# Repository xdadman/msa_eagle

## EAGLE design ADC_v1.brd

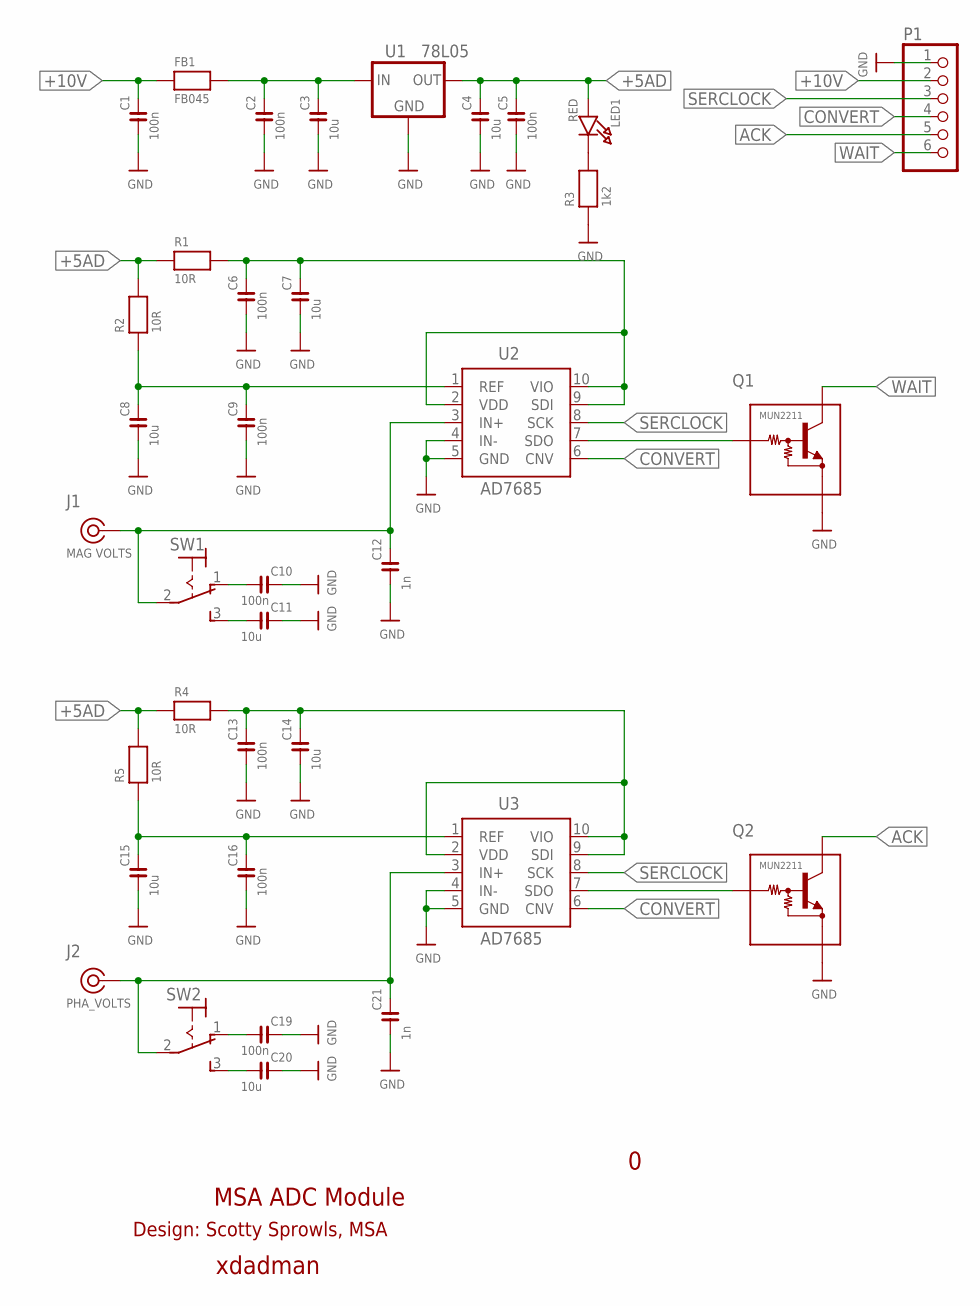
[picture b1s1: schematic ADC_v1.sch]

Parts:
C1, C2, C5, C6, C9, C10, C13, C16, C19: 100n; C0805
C3, C4, C7, C8, C11, C14, C15, C20: 10u; C1206
C12, C21: 1n; C0805
FB1: FB045; R0805
J1: MAG VOLTS; SLIM_COAX_PAD
J2: PHA_VOLTS; SLIM_COAX_PAD
LED1: RED; CHIPLED_0603
P1: PINHD-1X6; 1X06
Q1, Q2: MUN2211; SOT23
R1, R2, R4, R5: 10R; R0805
R3: 1k2; R0805
SW1, SW2: SWITCH1AS3; 1AS3T2B4M2RE
U1: 78L05; SOT89
U2, U3: AD7685; MSOP10

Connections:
+5AD: C4.2, C5.2, LED1.A, R1.1, R2.2, R4.1, R5.2, U1.1 (OUT)
+10V: C1.2, FB1.1, P1.2
ACK: P1.5, Q2.C
CONVERT: P1.4, U2.6 (CNV), U3.6 (CNV)
GND: C1.1, C2.1, C3.1, C4.1, C5.1, C6.1, C7.1, C8.1, C9.1, C10.2, C11.2, C12.1, C13.1, C14.1, C15.1, C16.1, C19.2, C20.2, C21.1, J1.GND, J2.GND, P1.1, Q1.E, Q2.E, R3.1, U1.2 (GND), U1.4 (GND), U2.4 (IN-), U2.5 (GND), U3.4 (IN-), U3.5 (GND)
unnamed: C2.2, C3.2, FB1.2, U1.3 (IN)
unnamed: C8.2, C9.2, R2.1, U2.1 (REF)
unnamed: C6.2, C7.2, R1.2, U2.2 (VDD), U2.9 (SDI), U2.10 (VIO)
unnamed: LED1.C, R3.2
unnamed: Q1.B, U2.7 (SDO)
unnamed: C15.2, C16.2, R5.1, U3.1 (REF)
unnamed: C12.2, J1.SIG (1), SW1.2, U2.3 (IN+)
unnamed: C11.1, SW1.3 (S)
unnamed: C10.1, SW1.1 (O)
unnamed: C13.2, C14.2, R4.2, U3.2 (VDD), U3.9 (SDI), U3.10 (VIO)
unnamed: Q2.B, U3.7 (SDO)
unnamed: C21.2, J2.SIG (1), SW2.2, U3.3 (IN+)
unnamed: C20.1, SW2.3 (S)
unnamed: C19.1, SW2.1 (O)
SERCLOCK: P1.3, U2.8 (SCK), U3.8 (SCK)
WAIT: P1.6, Q1.C

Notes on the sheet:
xdadman
MSA ADC Module
Design: Scotty Sprowls, MSA

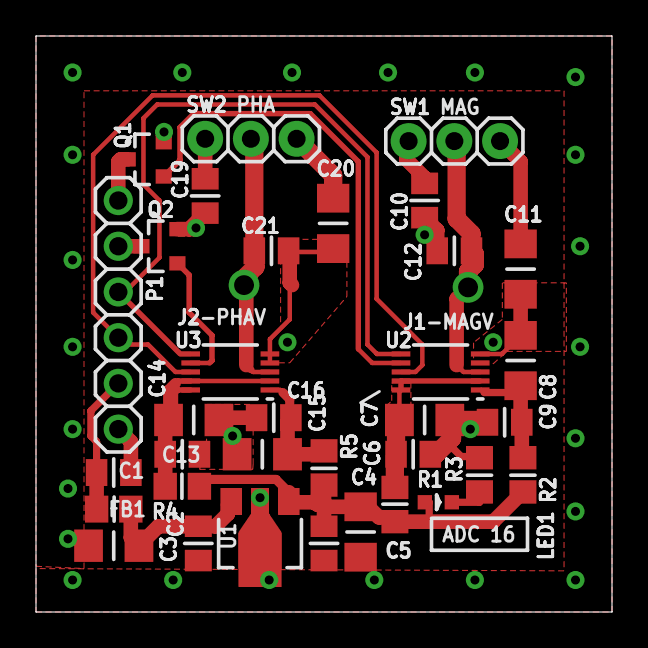
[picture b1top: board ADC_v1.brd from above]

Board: 2 copper layers, 32.0 x 32.0 mm, 36 parts (0 on the bottom side), 21 nets.

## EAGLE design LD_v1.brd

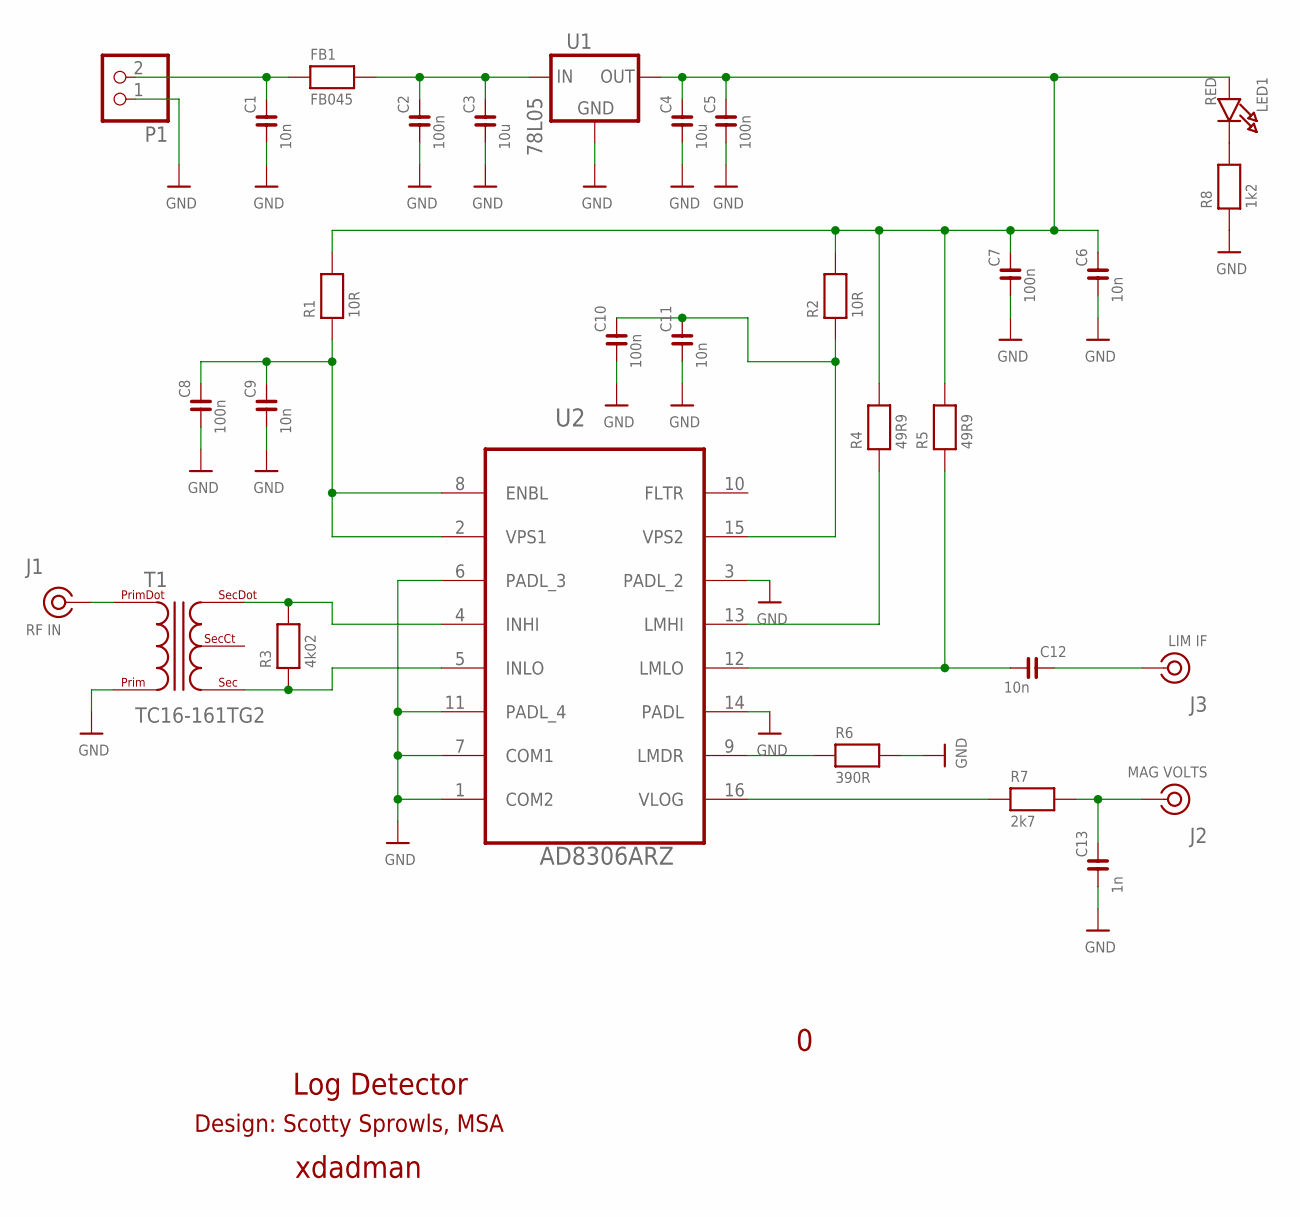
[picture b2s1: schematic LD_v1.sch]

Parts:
C1, C6, C9, C11, C12: 10n; C0805
C2, C5, C7, C8, C10: 100n; C0805
C3, C4: 10u; C1206
C13: 1n; C0805
FB1: FB045; R0805
J1: RF IN; SLIM_COAX_PAD
J2: MAG VOLTS; SLIM_COAX_PAD
J3: LIM IF; SLIM_COAX_PAD
LED1: RED; CHIPLED_0603
P1: PINHD-1X2; 1X02
R1, R2: 10R; R0805
R3: 4k02; R0805
R4, R5: 49R9; R0805
R6: 390R; R0805
R7: 2k7; R0805
R8: 1k2; R0805
T1: TC16-161TG2
U1: 78L05; SOT89
U2: AD8306ARZ; SOIC16

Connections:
+5V: C4.2, C5.2, C6.2, C7.2, LED1.A, R1.2, R2.2, R4.2, R5.2, U1.1 (OUT)
+10V: C1.2, FB1.1, P1.2
GND: C1.1, C2.1, C3.1, C4.1, C5.1, C6.1, C7.1, C8.1, C9.1, C10.1, C11.1, C13.1, J1.GND, J2.GND, J3.GND, P1.1, R6.2, R8.1, T1.4, U1.2 (GND), U1.4 (GND), U2.1 (COM2), U2.3 (PADL_2), U2.6 (PADL_3), U2.7 (COM1), U2.11 (PADL_4), U2.14 (PADL)
unnamed: C2.2, C3.2, FB1.2, U1.3 (IN)
unnamed: C8.2, C9.2, R1.1, U2.2 (VPS1), U2.8 (ENBL)
unnamed: R4.1, U2.13 (LMHI)
unnamed: C13.2, J2.SIG (1), R7.2
unnamed: C12.1, R5.1, U2.12 (LMLO)
unnamed: C12.2, J3.SIG (1)
unnamed: R3.2, T1.1, U2.4 (INHI)
unnamed: R3.1, T1.3, U2.5 (INLO)
unnamed: J1.SIG (1), T1.6
unnamed: R6.1, U2.9 (LMDR)
unnamed: R7.1, U2.16 (VLOG)
unnamed: LED1.C, R8.2
unnamed: C10.2, C11.2, R2.1, U2.15 (VPS2)

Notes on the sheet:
xdadman
Log Detector
Design: Scotty Sprowls, MSA

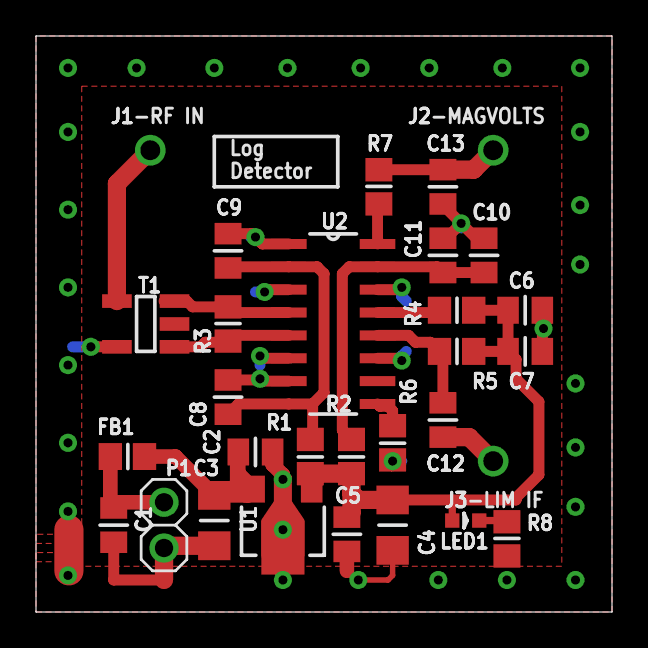
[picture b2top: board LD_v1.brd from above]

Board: 2 copper layers, 32.0 x 32.0 mm, 30 parts (0 on the bottom side), 16 nets.

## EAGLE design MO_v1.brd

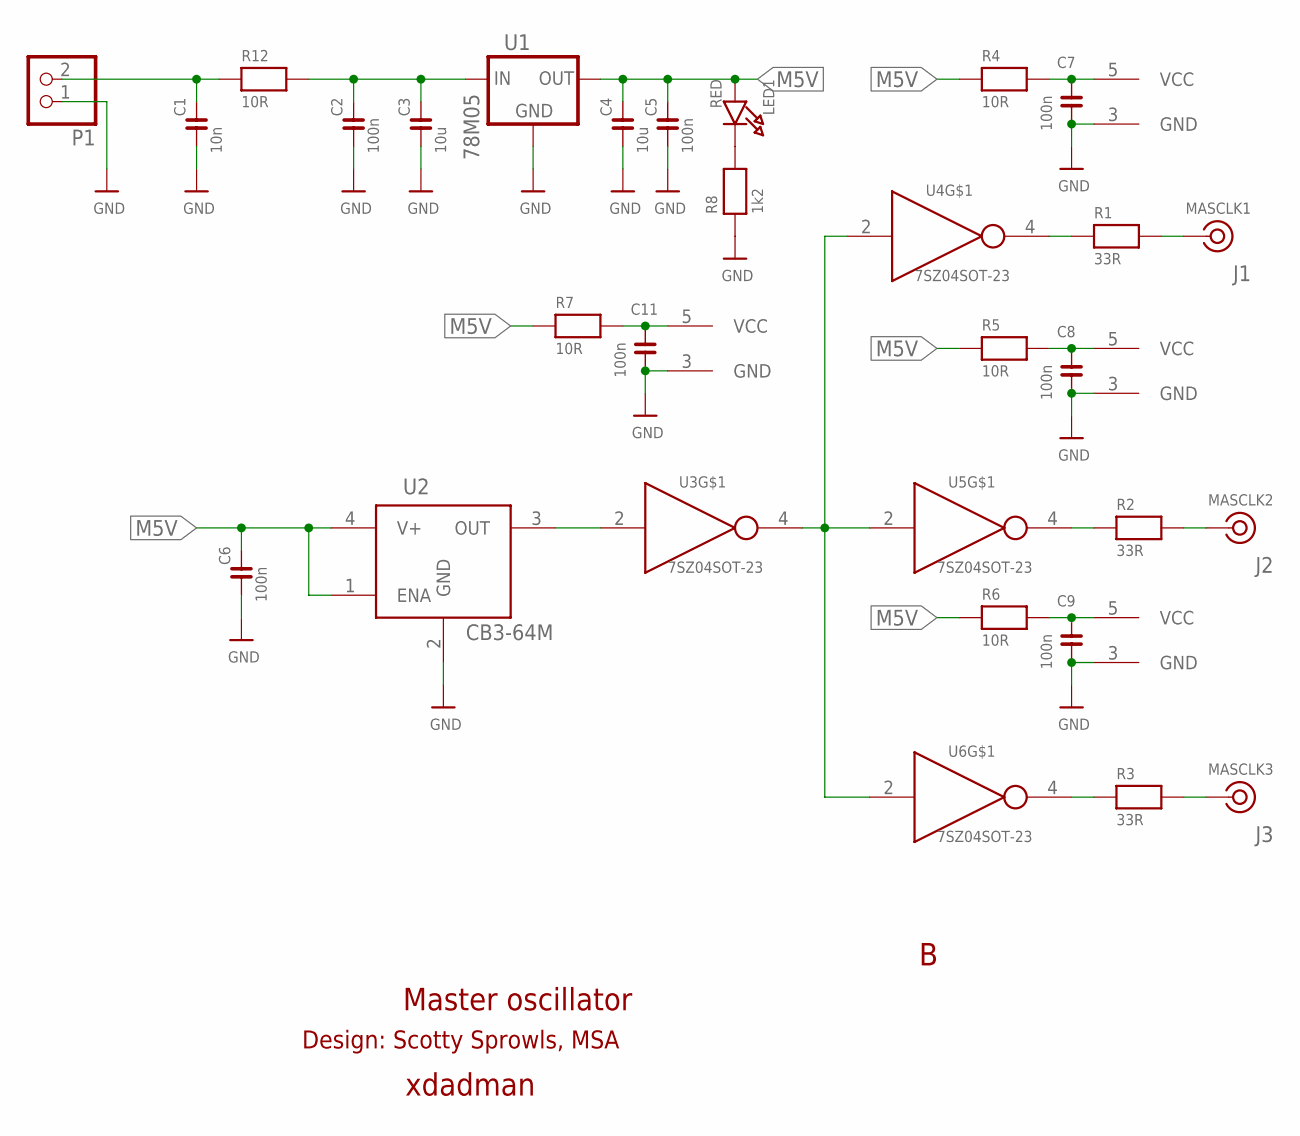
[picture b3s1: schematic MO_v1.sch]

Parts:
C1: 10n; C0805
C2, C5, C6, C7, C8, C9, C11: 100n; C0805
C3, C4: 10u; C1206
J1: MASCLK1; SLIM_COAX_PAD
J2: MASCLK2; SLIM_COAX_PAD
J3: MASCLK3; SLIM_COAX_PAD
LED1: RED; CHIPLED_0603
P1: PINHD-1X2; 1X02
R1, R2, R3: 33R; R0805
R4, R5, R6, R7, R12: 10R; R0805
R8: 1k2; R0805
U1: 78M05; TO252
U2: CB3-64M
U3, U4, U5, U6: 7SZ04SOT-23; SOT23-5L

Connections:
+10V: C1.2, P1.2, R12.1
GND: C1.1, C2.1, C3.1, C4.1, C5.1, C6.1, C7.1, C8.1, C9.1, C11.1, J1.GND, J2.GND, J3.GND, P1.1, R8.1, U1.3 (GND), U2.2 (GND), U3.3 (GND), U4.3 (GND), U5.3 (GND), U6.3 (GND)
M5V: C4.2, C5.2, C6.2, LED1.A, R4.1, R5.1, R6.1, R7.1, U1.2 (OUT), U2.1 (ENA), U2.4 (V+)
unnamed: C2.2, C3.2, R12.2, U1.1 (IN)
unnamed: U2.3 (OUT), U3.2 (IN)
unnamed: C7.2, R4.2, U4.5 (VCC)
unnamed: C11.2, R7.2, U3.5 (VCC)
unnamed: C8.2, R5.2, U5.5 (VCC)
unnamed: U3.4 (OUT), U4.2 (IN), U5.2 (IN), U6.2 (IN)
unnamed: C9.2, R6.2, U6.5 (VCC)
unnamed: R1.1, U4.4 (OUT)
unnamed: R2.1, U5.4 (OUT)
unnamed: R3.1, U6.4 (OUT)
unnamed: J3.SIG (1), R3.2
unnamed: J2.SIG (1), R2.2
unnamed: J1.SIG (1), R1.2
unnamed: LED1.C, R8.2

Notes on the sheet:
xdadman
Master oscillator
Design: Scotty Sprowls, MSA

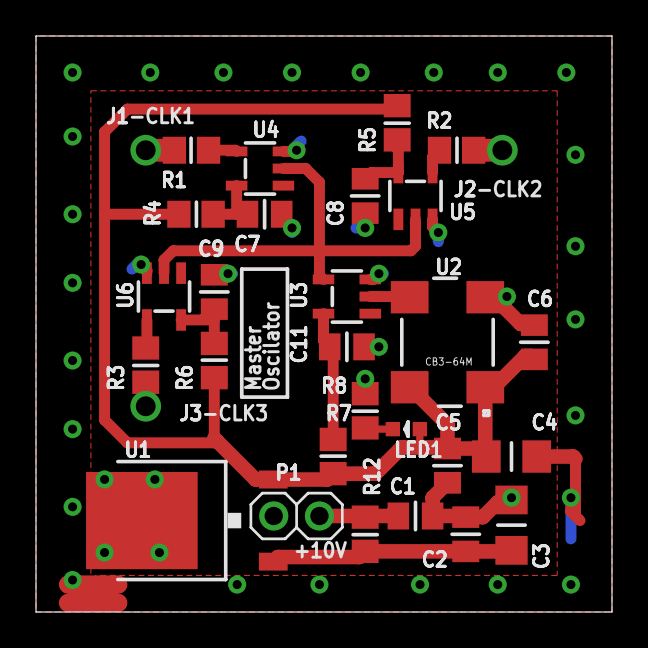
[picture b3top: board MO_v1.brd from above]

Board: 2 copper layers, 32.0 x 32.0 mm, 30 parts (0 on the bottom side), 17 nets.

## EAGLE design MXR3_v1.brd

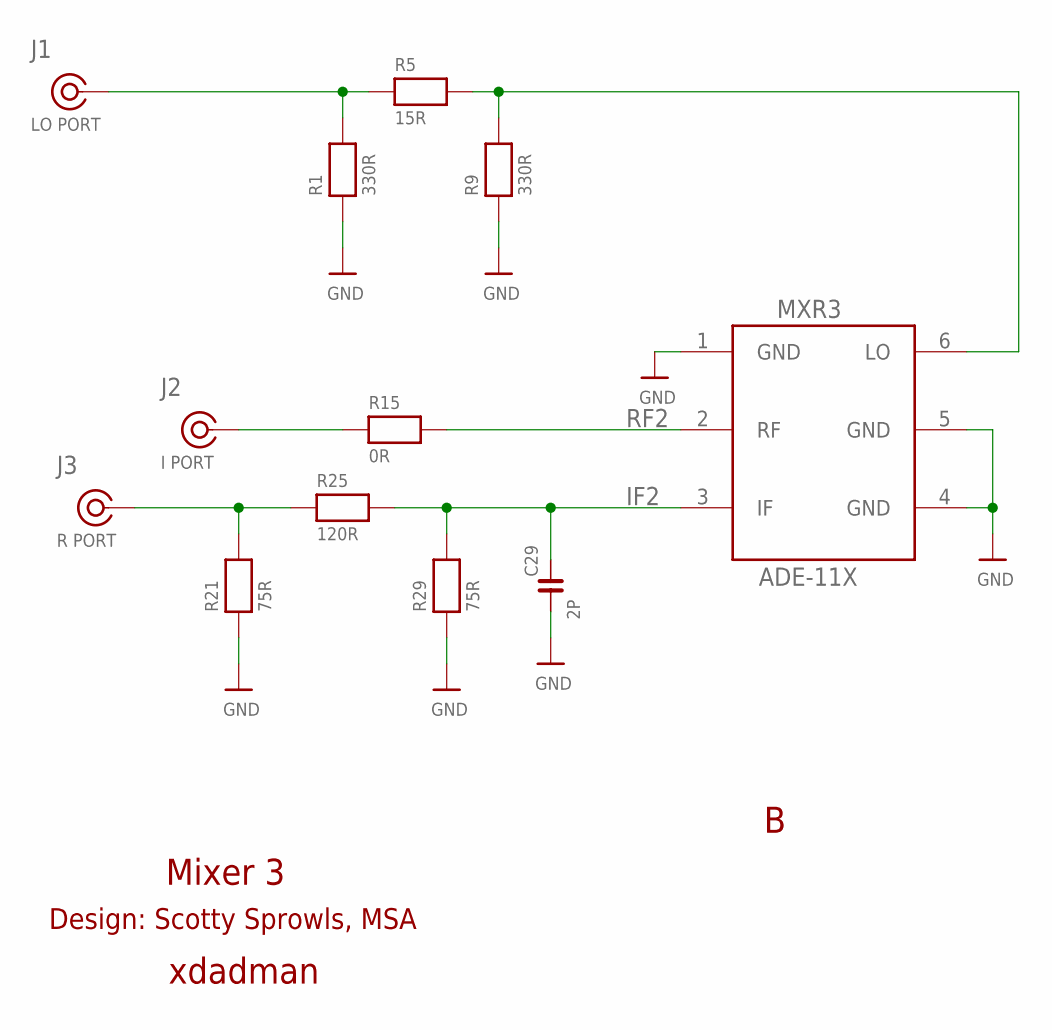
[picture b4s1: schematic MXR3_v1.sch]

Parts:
C29: 2P; C0603
J1: LO PORT; SLIM_COAX_PAD
J2: I PORT; SLIM_COAX_PAD
J3: R PORT; SLIM_COAX_PAD
MXR3: ADE-11X
R1, R9: 330R; R0805
R5: 15R; 0805
R15: 0R; R0805
R21, R29: 75R; R0805
R25: 120R; R0805

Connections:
GND: C29.1, J1.GND, J2.GND, J3.GND, MXR3.1 (GND), MXR3.4 (GND), MXR3.5 (GND), R1.1, R9.1, R21.1, R29.1
IF: J3.SIG (1), R21.2, R25.1
IF2: C29.2, MXR3.3 (IF), R25.2, R29.2
LO: J1.SIG (1), R1.2, R5.1
LO3: MXR3.6 (LO), R5.2, R9.2
RF: J2.SIG (1), R15.1
RF2: MXR3.2 (RF), R15.2

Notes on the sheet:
xdadman
Mixer 3
Design: Scotty Sprowls, MSA

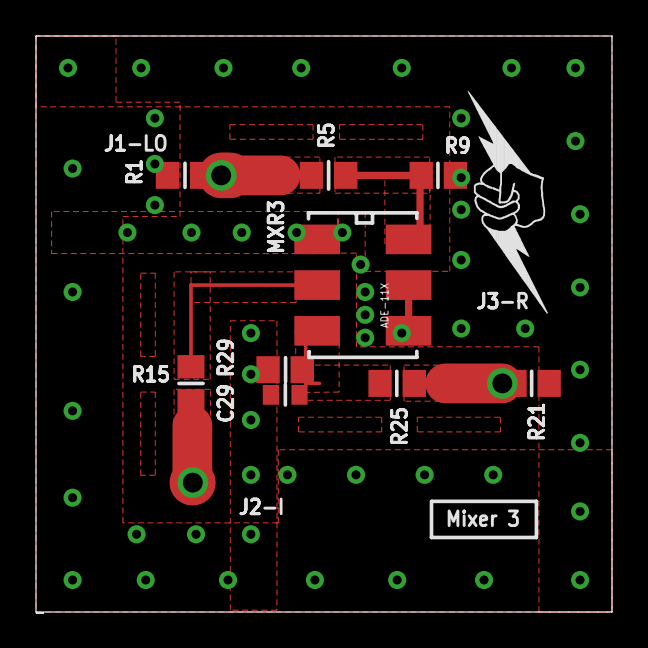
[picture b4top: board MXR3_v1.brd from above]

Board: 2 copper layers, 32.0 x 32.0 mm, 12 parts (0 on the bottom side), 7 nets.

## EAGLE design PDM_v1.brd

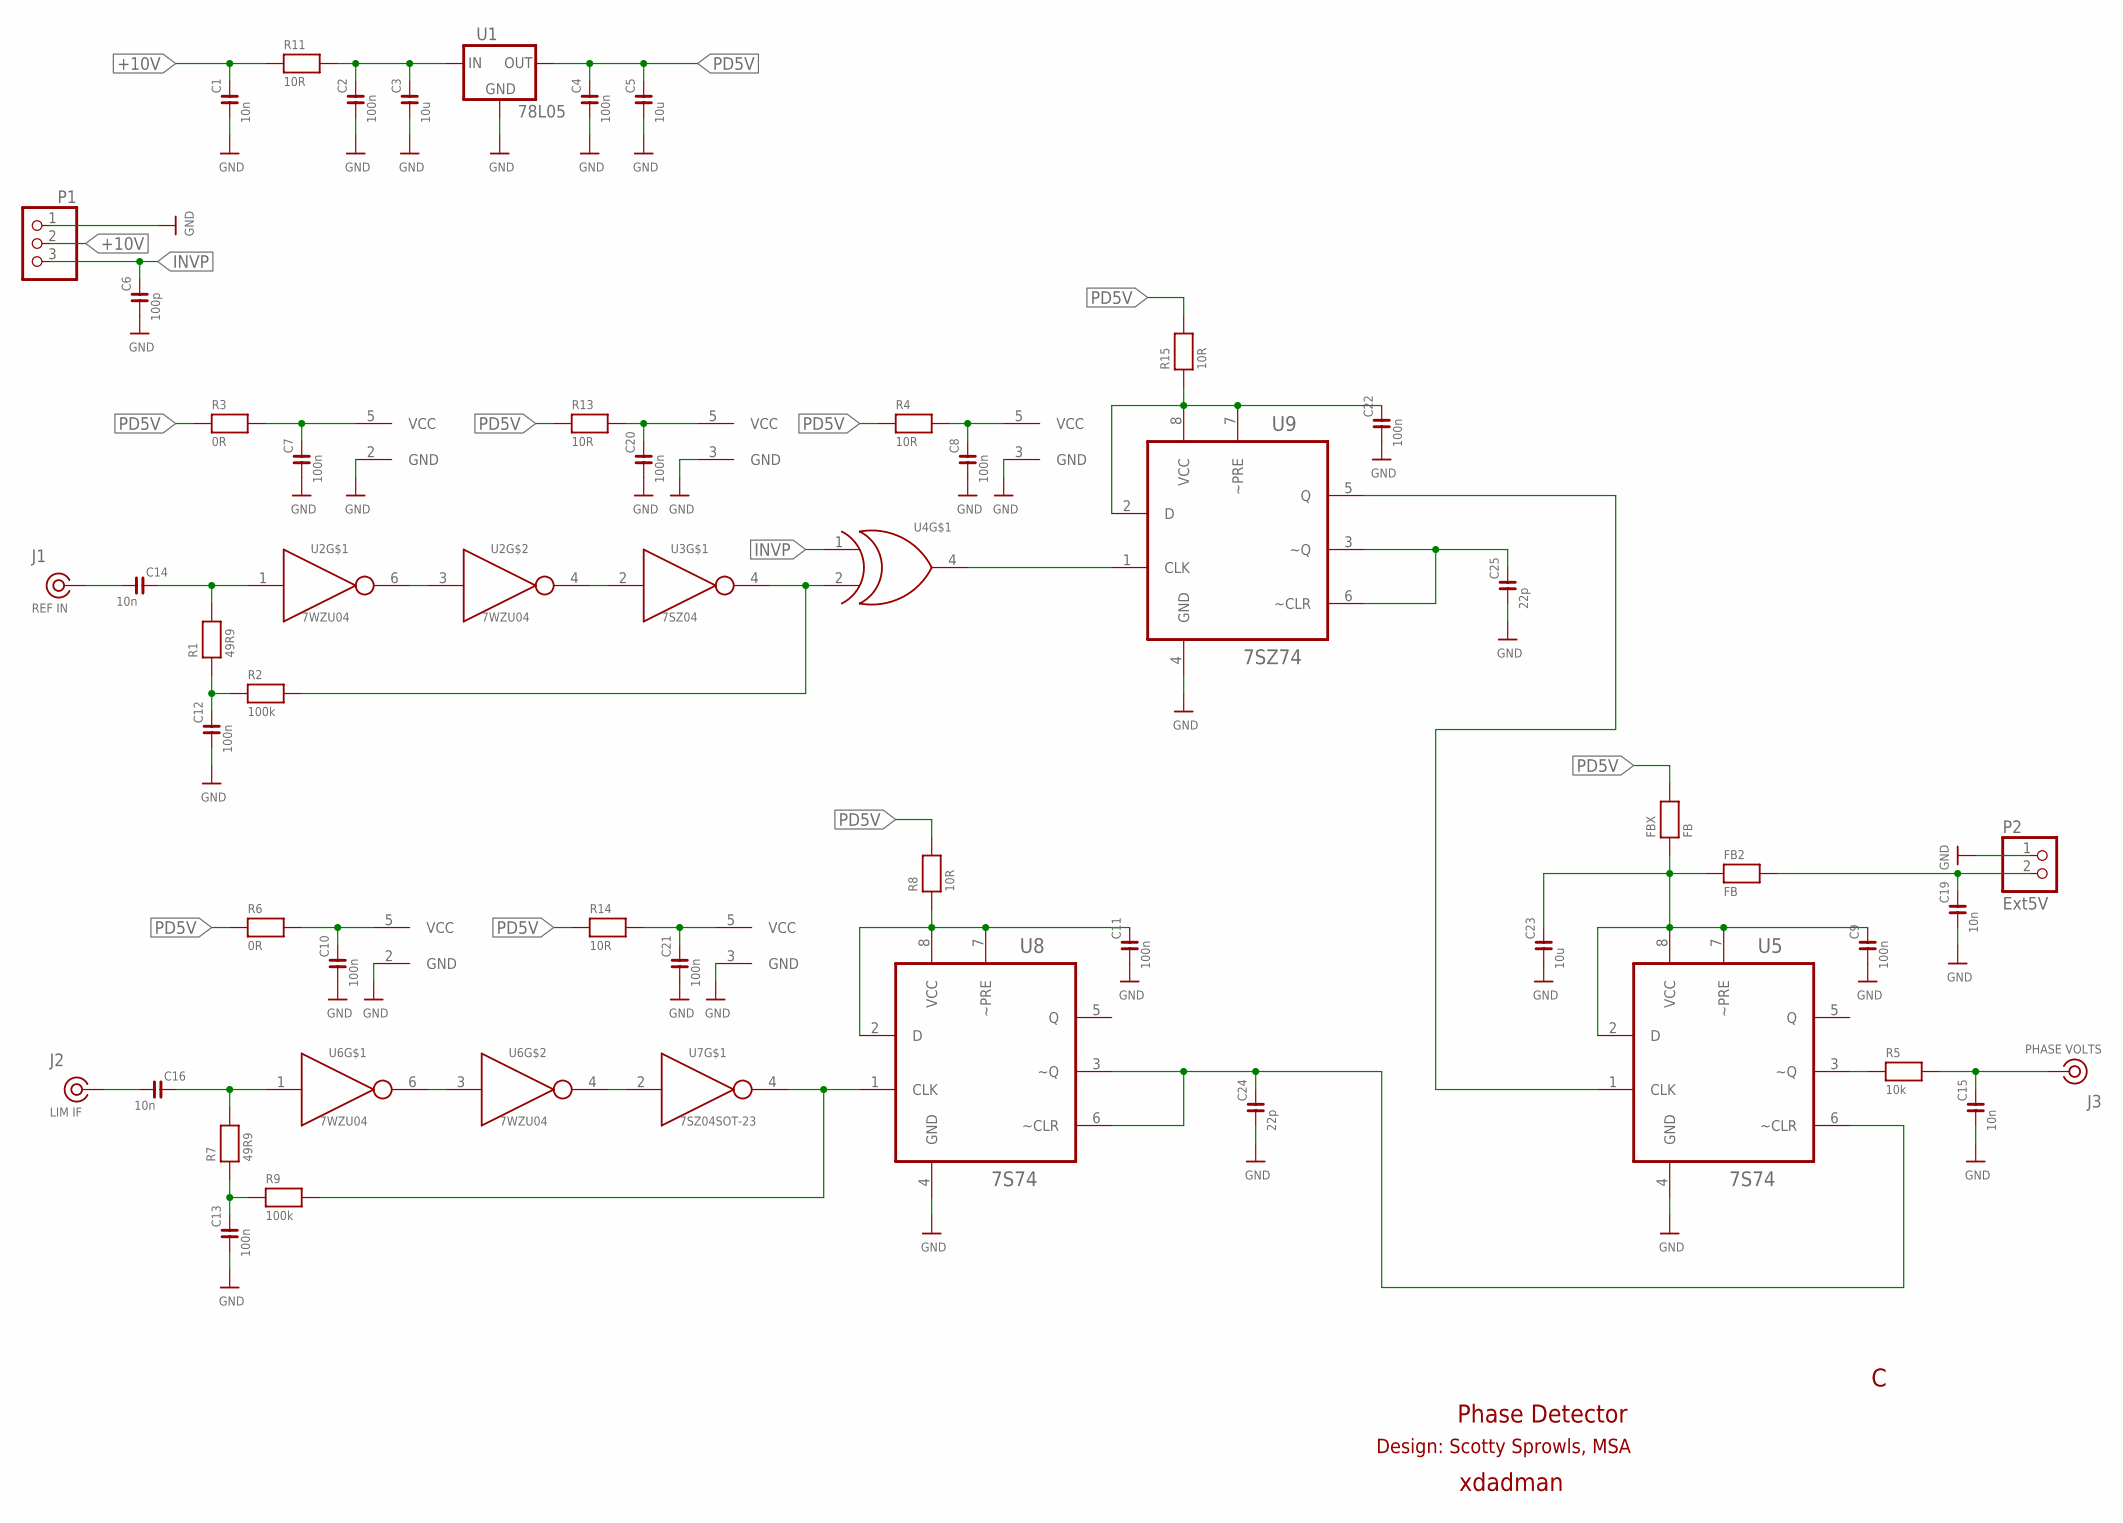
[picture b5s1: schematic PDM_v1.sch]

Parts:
C1, C14, C15, C16, C19: 10n; C0805
C2, C4, C7, C8, C9, C10, C11, C12, C13, C20, C21, C22: 100n; C0805
C3, C5, C23: 10u; C1206
C6: 100p; C0805
C24, C25: 22p; C0603
FB2: FB; R0805
FBX: FB; R0805
J1: REF IN; SLIM_COAX_PAD
J2: LIM IF; SLIM_COAX_PAD
J3: PHASE VOLTS; SLIM_COAX_PAD
P1: PINHD-1X3; 1X03
P2: Ext5V; 1X02
R1, R7: 49R9; R0805
R2, R9: 100k; R0805
R3, R6: 0R; R0805
R4, R8, R11, R13, R14, R15: 10R; R0805
R5: 10k; R0805
U1: 78L05; SOT89
U2, U6: 7WZU04; SC70-6L
U3: 7SZ04; SOT23-5L
U4: 74LVC1G86; SOT23-5L
U5, U8: 7S74; SOP50P310X90-8N
U7: 7SZ04SOT-23; SOT23-5L
U9: 7SZ74; SOP50P310X90-8N

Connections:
+10V: C1.2, P1.2, R11.1
GND: C1.1, C2.1, C3.1, C4.1, C5.1, C6.1, C7.1, C8.1, C9.1, C10.1, C11.1, C12.1, C13.1, C15.1, C19.1, C20.1, C21.1, C22.1, C23.1, C24.1, C25.1, J1.GND, J2.GND, J3.GND, P1.1, P2.1, U1.2 (GND), U1.4 (GND), U2.2 (GND), U3.3 (GND), U4.3 (GND), U5.4 (GND), U6.2 (GND), U7.3 (GND), U8.4 (GND), U9.4 (GND)
INVP: C6.2, P1.3, U4.1 (A)
unnamed: C2.2, C3.2, R11.2, U1.3 (IN)
unnamed: C14.2, R1.2, U2.1 (IN)
unnamed: C12.2, R1.1, R2.1
unnamed: U2.3 (IN), U2.6 (OUT)
unnamed: R2.2, U3.4 (OUT), U4.2 (B)
unnamed: C20.2, R13.2, U3.5 (VCC)
unnamed: U2.4 (OUT), U3.2 (IN)
unnamed: C8.2, R4.2, U4.5 (VCC)
unnamed: U4.4 (Y), U9.1 (CLK)
unnamed: C22.2, R15.1, U9.2 (D), U9.7 (~PRE), U9.8 (VCC)
unnamed: C25.2, U9.3 (~Q), U9.6 (~CLR)
unnamed: C16.2, R7.2, U6.1 (IN)
unnamed: C13.2, R7.1, R9.1
unnamed: U6.3 (IN), U6.6 (OUT)
unnamed: R9.2, U7.4 (OUT), U8.1 (CLK)
unnamed: C21.2, R14.2, U7.5 (VCC)
unnamed: U6.4 (OUT), U7.2 (IN)
unnamed: C10.2, R6.2, U6.5 (VCC)
unnamed: C11.2, R8.1, U8.2 (D), U8.7 (~PRE), U8.8 (VCC)
unnamed: C24.2, U5.6 (~CLR), U8.3 (~Q), U8.6 (~CLR)
unnamed: U5.1 (CLK), U9.5 (Q)
unnamed: C9.2, C23.2, FB2.1, FBX.1, U5.2 (D), U5.7 (~PRE), U5.8 (VCC)
unnamed: C15.2, J3.SIG (1), R5.2
unnamed: C14.1, J1.SIG (1)
unnamed: C7.2, R3.2, U2.5 (VCC)
unnamed: C16.1, J2.SIG (1)
unnamed: R5.1, U5.3 (~Q)
P2: C19.2, FB2.2, P2.2
PD5V: C4.2, C5.2, FBX.2, R3.1, R4.1, R6.1, R8.2, R13.1, R14.1, R15.2, U1.1 (OUT)

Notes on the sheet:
xdadman
Phase Detector
Design: Scotty Sprowls, MSA

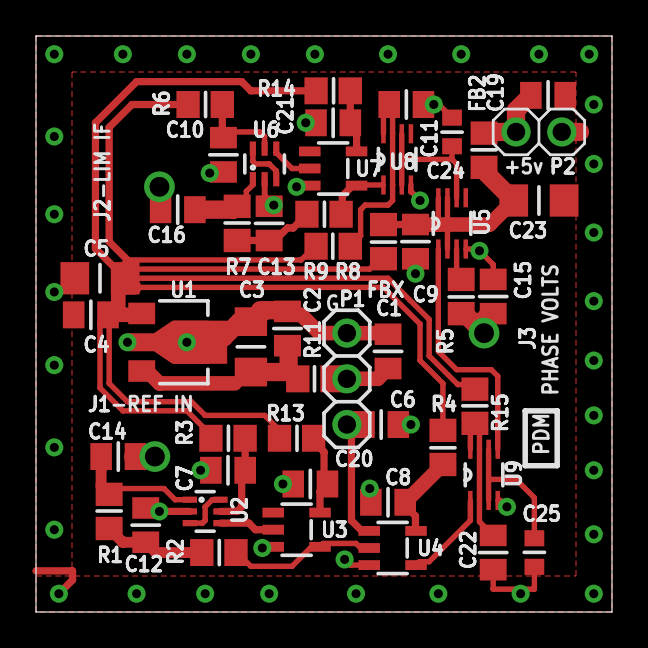
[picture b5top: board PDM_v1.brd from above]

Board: 2 copper layers, 32.0 x 32.0 mm, 52 parts (0 on the bottom side), 32 nets.

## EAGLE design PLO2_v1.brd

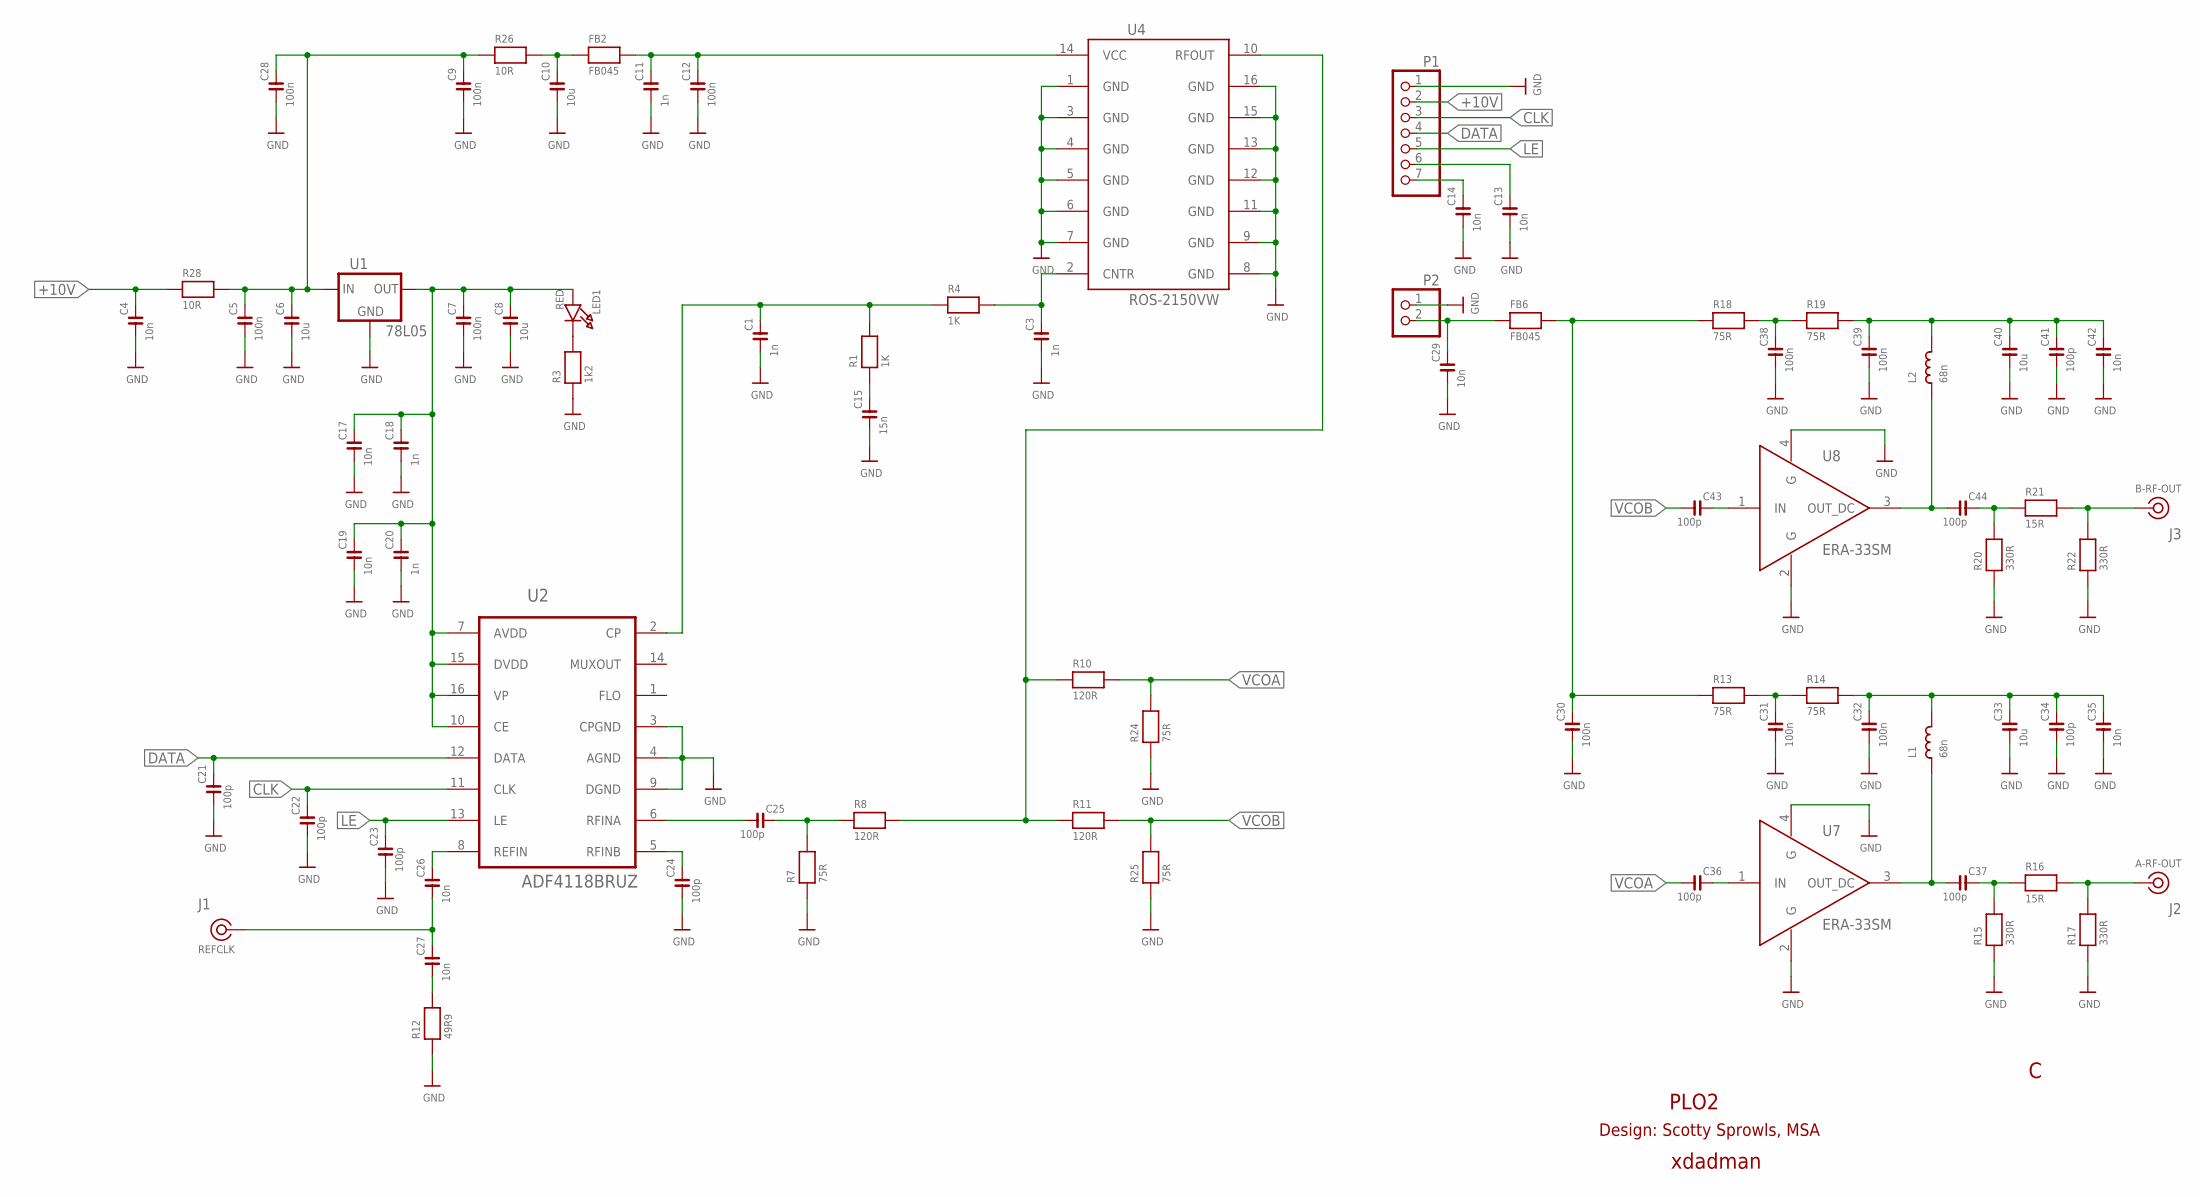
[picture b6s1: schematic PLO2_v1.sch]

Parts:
C1, C3, C11, C18, C20: 1n; C0805
C4, C13, C14, C17, C19, C26, C27, C29, C35, C42: 10n; C0805
C5, C7, C9, C12, C28, C30, C31, C32, C38, C39: 100n; C0805
C6, C8, C10, C33, C40: 10u; C1206
C15: 15n; C0805
C21, C22, C23, C24, C25, C34, C36, C37, C41, C43, C44: 100p; C0805
FB2: FB045; R0805_SPC
FB6: FB045; R0805
J1: REFCLK; SLIM_COAX_PAD
J2: A-RF-OUT; SLIM_COAX_PAD
J3: B-RF-OUT; SLIM_COAX_PAD
L1, L2: 68n; 0603-MINI
LED1: RED; CHIPLED_0603
P1: PINHD-1X7; 1X07
P2: PINHD-1X2; 1X02
R1, R4: 1K; R0805
R3: 1k2; R0805
R7, R13, R14, R18, R19, R24, R25: 75R; R0805
R8, R10, R11: 120R; R0805
R12: 49R9; R0805
R15, R17, R20, R22: 330R; R0805
R16, R21: 15R; 0805
R26, R28: 10R; R0805
U1: 78L05; SOT89
U2: ADF4118BRUZ; SOIC65P640X120-16N
U4: ROS-2150VW
U7, U8: ERA-33SM; WW107

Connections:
+10V: C4.2, P1.2, R28.1
+20V: C13.2, P1.6
CLK: C22.2, P1.3, U2.11 (CLK)
DATA: C21.2, P1.4, U2.12 (DATA)
DATA1: C24.2, U2.5 (RFINB)
DATA2: C39.2, C40.2, C41.2, C42.2, L2.2, R19.2
DATA3: C32.2, C33.2, C34.2, C35.2, L1.2, R14.2
GND: C1.1, C3.1, C4.1, C5.1, C6.1, C7.1, C8.1, C9.1, C10.1, C11.1, C12.1, C13.1, C14.1, C15.1, C17.1, C18.1, C19.1, C20.1, C21.1, C22.1, C23.1, C24.1, C28.1, C29.1, C30.1, C31.1, C32.1, C33.1, C34.1, C35.1, C38.1, C39.1, C40.1, C41.1, C42.1, J1.GND, J2.GND, J3.GND, P1.1, P2.1, R3.1, R7.1, R12.1, R15.1, R17.1, R20.1, R22.1, R24.1, R25.1, U1.2 (GND), U1.4 (GND), U2.3 (CPGND), U2.4 (AGND), U2.9 (DGND), U4.1 (GND), U4.3 (GND), U4.4 (GND), U4.5 (GND), U4.6 (GND), U4.7 (GND), U4.8 (GND), U4.9 (GND), U4.11 (GND), U4.12 (GND), U4.13 (GND), U4.15 (GND), U4.16 (GND), U7.2 (G), U7.4 (G), U8.2 (G), U8.4 (G)
LE: C23.2, P1.5, U2.13 (LE)
unnamed: C5.2, C6.2, C9.2, C28.2, R26.1, R28.2, U1.3 (IN)
unnamed: C1.2, R1.2, R4.1, U2.2 (CP)
unnamed: C10.2, FB2.1, R26.2
unnamed: C11.2, C12.2, FB2.2, U4.14 (VCC)
unnamed: C15.2, R1.1
unnamed: LED1.C, R3.2
unnamed: C3.2, R4.2, U4.2 (CNTR)
unnamed: C26.2, U2.8 (REFIN)
unnamed: C26.1, C27.2, J1.SIG (1)
unnamed: C27.1, R12.2
unnamed: C25.2, R7.2, R8.1
unnamed: C25.1, U2.6 (RFINA)
unnamed: R8.2, R10.1, R11.1, U4.10 (RFOUT)
unnamed: C30.2, FB6.2, R13.1, R18.1
unnamed: C29.2, FB6.1, P2.2
unnamed: C38.2, R18.2, R19.1
unnamed: C44.2, R20.2, R21.1
unnamed: J3.SIG (1), R21.2, R22.2
unnamed: C14.2, P1.7
unnamed: C44.1, L2.1, U8.3 (OUT_DC)
unnamed: C43.2, U8.1 (IN)
unnamed: C31.2, R13.2, R14.1
unnamed: C37.2, R15.2, R16.1
unnamed: J2.SIG (1), R16.2, R17.2
unnamed: C37.1, L1.1, U7.3 (OUT_DC)
unnamed: C36.2, U7.1 (IN)
PLO5V: C7.2, C8.2, C17.2, C18.2, C19.2, C20.2, LED1.A, U1.1 (OUT), U2.7 (AVDD), U2.10 (CE), U2.15 (DVDD), U2.16 (VP)
VCOA: C36.1, R10.2, R24.2
VCOB: C43.1, R11.2, R25.2

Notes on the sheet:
xdadman
PLO2
Design: Scotty Sprowls, MSA

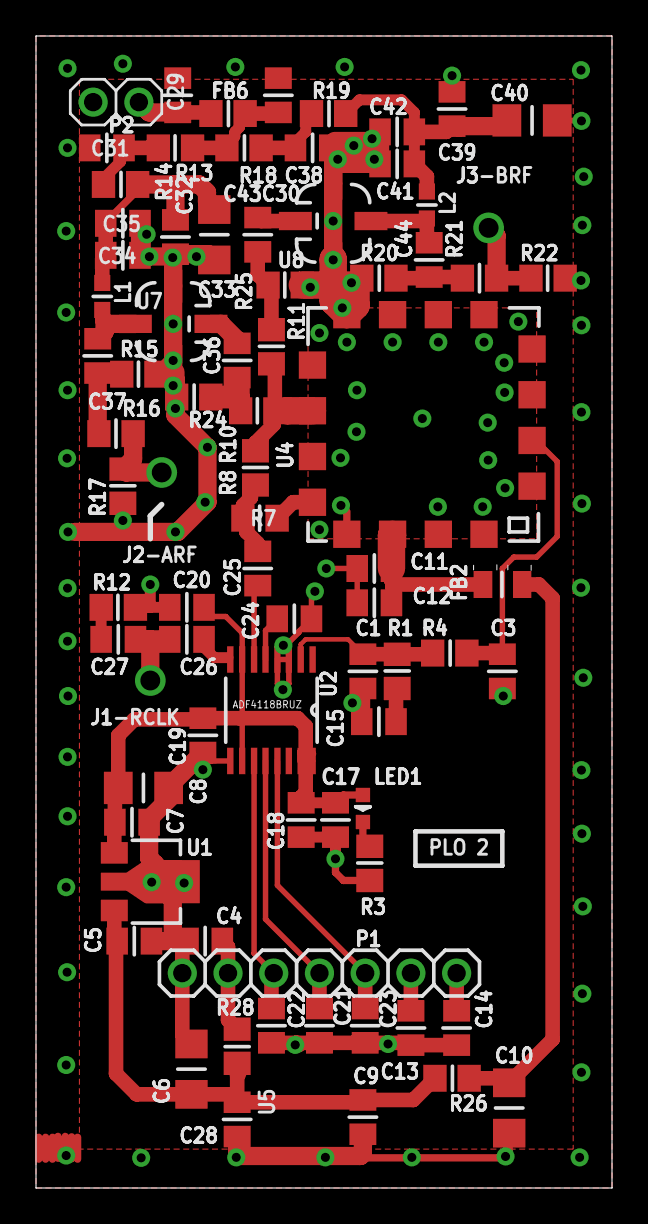
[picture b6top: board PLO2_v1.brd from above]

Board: 2 copper layers, 32.0 x 64.0 mm, 79 parts (0 on the bottom side), 38 nets.
